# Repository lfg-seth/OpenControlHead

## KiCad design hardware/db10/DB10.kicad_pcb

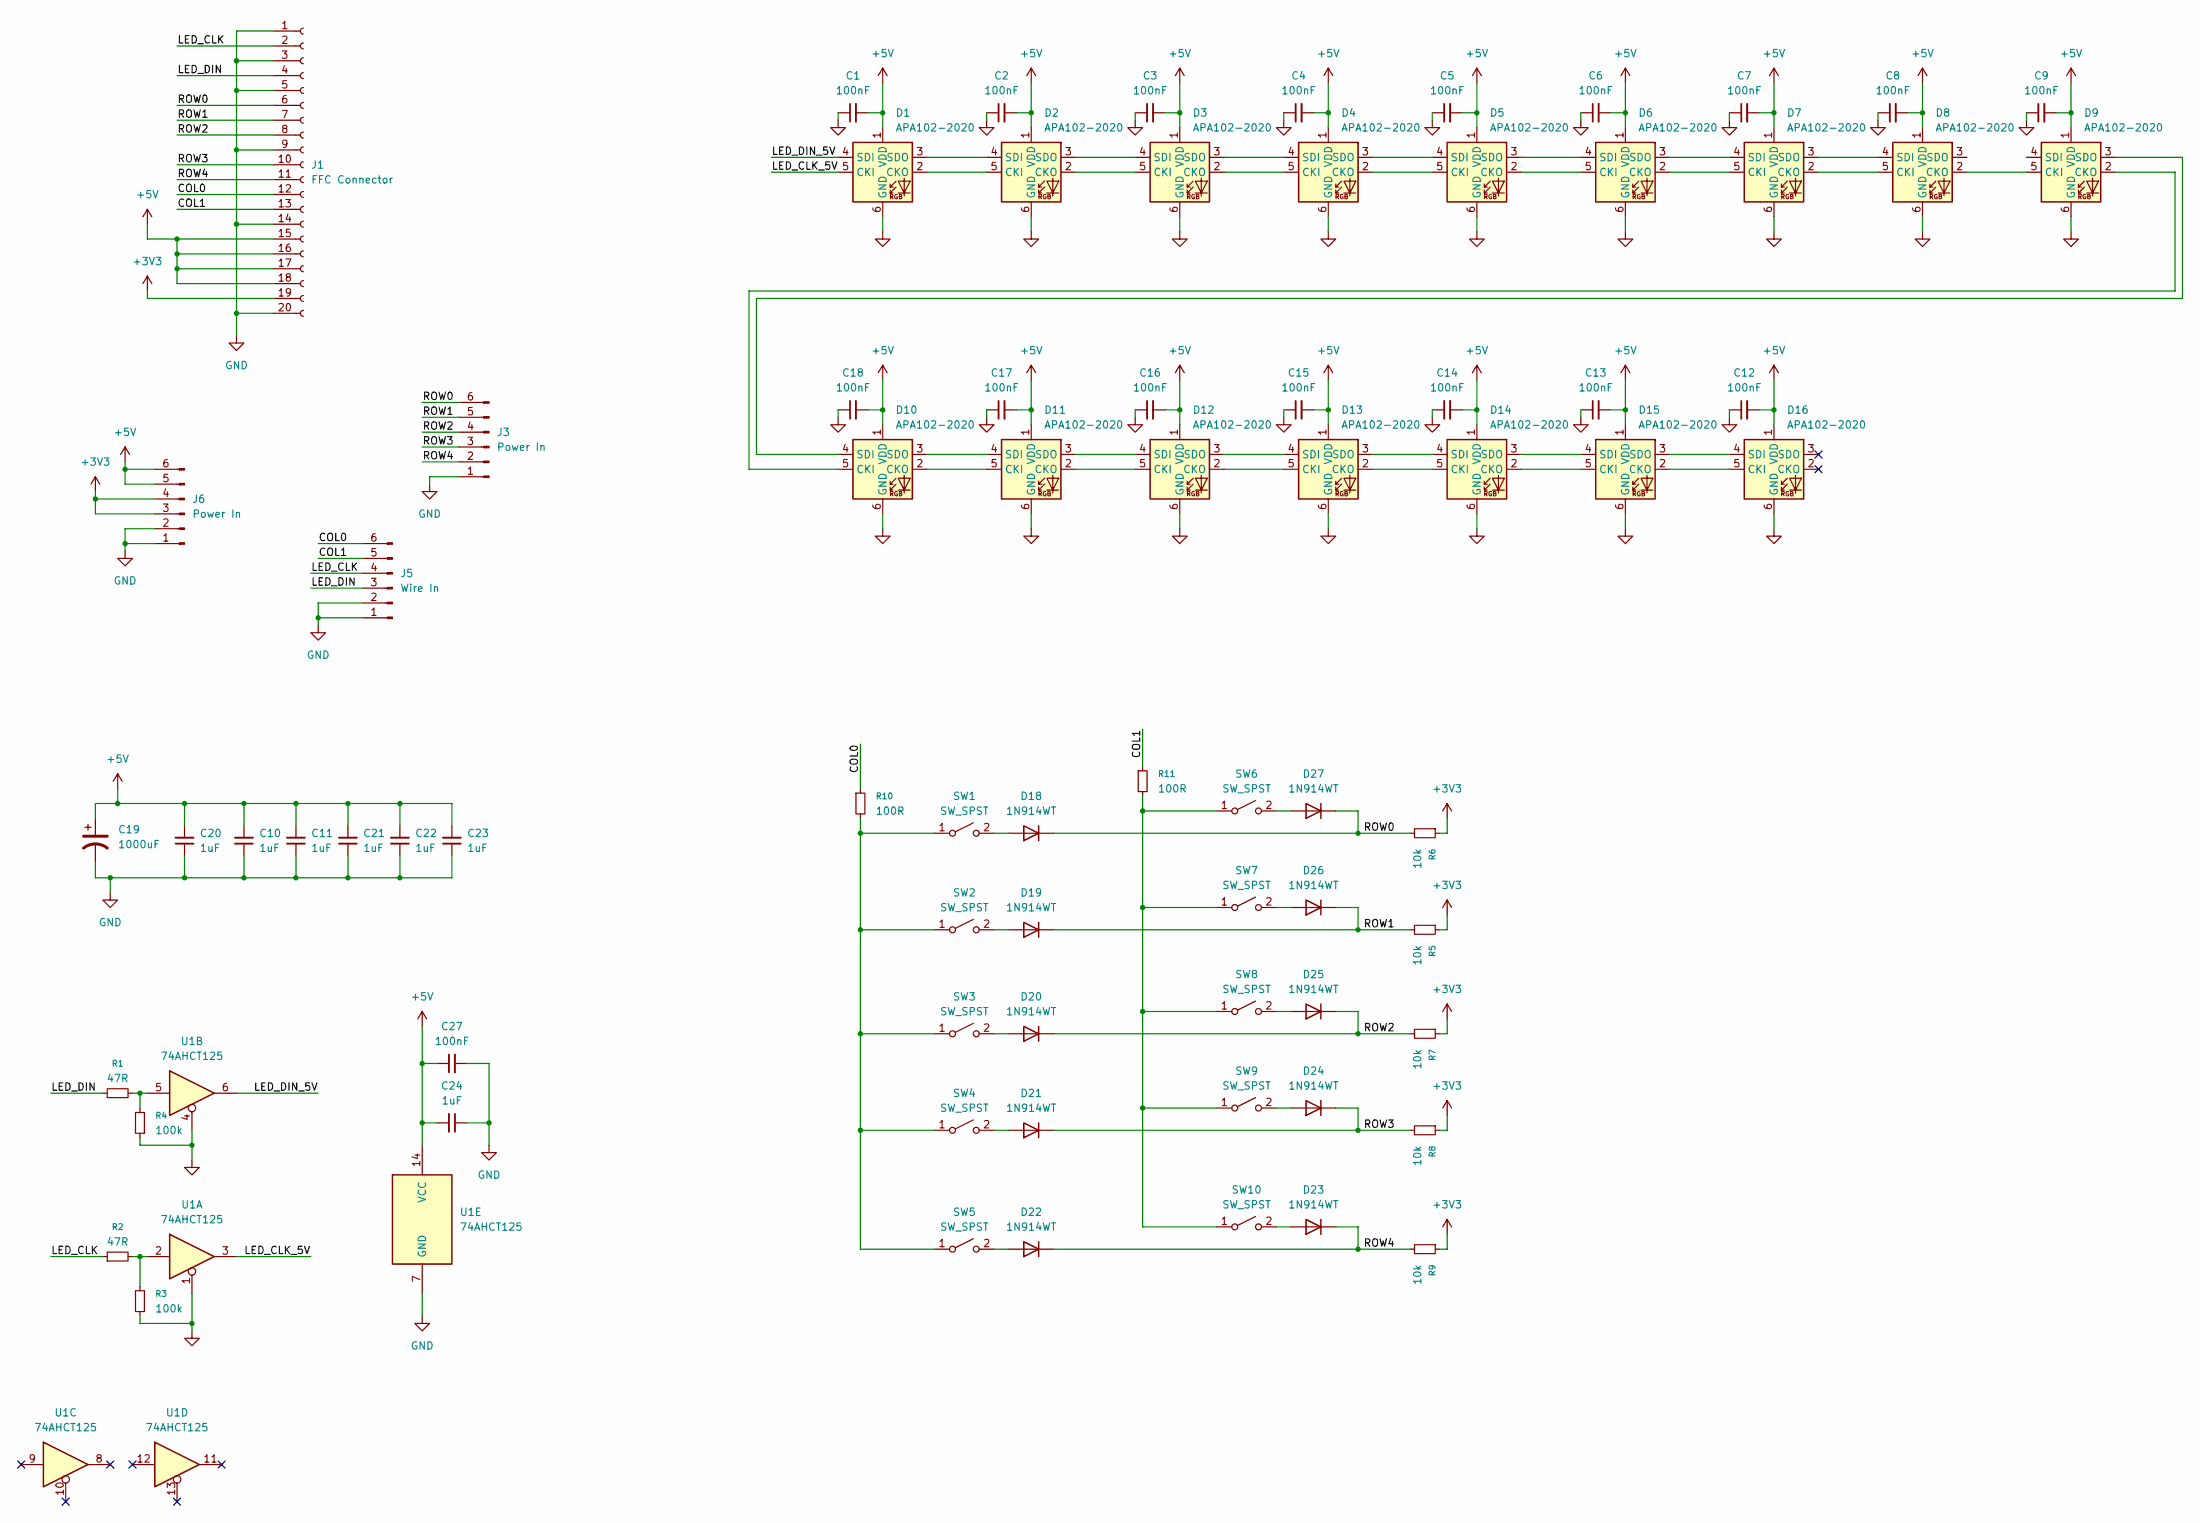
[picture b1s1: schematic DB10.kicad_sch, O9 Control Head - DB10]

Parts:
C1, C2, C3, C4, C5, C6, C7, C8, C9, C12, C13, C14, C15, C16, C17, C18, C27: 100nF; C_0603_1608Metric_Pad1.08x0.95mm_HandSolder
C10, C11, C20, C21, C22, C23, C24: 1uF; C_0603_1608Metric_Pad1.08x0.95mm_HandSolder
C19: 1000uF; CP_Elec_8x6.7
D1, D2, D3, D4, D5, D6, D7, D8, D9, D10, D11, D12, D13, D14, D15, D16: APA102-2020; LED-APA102-2020
D18, D19, D20, D21, D22, D23, D24, D25, D26, D27: 1N914WT; D_SOD-323_HandSoldering
J1: FFC Connector; Hirose_FH12-20S-0.5SH_1x20-1MP_P0.50mm_Horizontal
J3, J6: Power In; SolderWire-0.5sqmm_1x06_P4.8mm_D0.9mm_OD2.3mm
J5: Wire In; SolderWire-0.5sqmm_1x06_P4.8mm_D0.9mm_OD2.3mm
R1, R2: 47R; R_0603_1608Metric_Pad0.98x0.95mm_HandSolder
R3, R4: 100k; R_0603_1608Metric_Pad0.98x0.95mm_HandSolder
R5, R6, R7, R8, R9: 10k; R_0603_1608Metric_Pad0.98x0.95mm_HandSolder
R10, R11: 100R; R_0603_1608Metric_Pad0.98x0.95mm_HandSolder
SW1, SW2, SW3, SW4, SW5, SW6, SW7, SW8, SW9, SW10: SW_SPST; SW_SPST_TL3342
U1: 74AHCT125; SOIC-14_3.9x8.7mm_P1.27mm

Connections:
+3V3: J1.19, J6.3, J6.4, R5.1, R6.1, R7.1, R8.1, R9.1
+5V: C1.2, C2.2, C3.2, C4.2, C5.2, C6.2, C7.2, C8.2, C9.2, C10.2, C11.2, C12.2, C13.2, C14.2, C15.2, C16.2, C17.2, C18.2, C19.1, C20.2, C21.2, C22.2, C23.2, C24.2, C27.1, D1.1 (VDD), D2.1 (VDD), D3.1 (VDD), D4.1 (VDD), D5.1 (VDD), D6.1 (VDD), D7.1 (VDD), D8.1 (VDD), D9.1 (VDD), D10.1 (VDD), D11.1 (VDD), D12.1 (VDD), D13.1 (VDD), D14.1 (VDD), D15.1 (VDD), D16.1 (VDD), J1.15, J1.16, J1.17, J1.18, J6.5, J6.6, U1.14 (VCC)
/COL0: J1.12, J5.6, R10.1
/COL1: J1.13, J5.5, R11.1
/LED_CLK: J1.2, J5.4, R2.1
/LED_CLK_5V: D1.5 (CKI), U1.3
/LED_DIN: J1.4, J5.3, R1.1
/LED_DIN_5V: D1.4 (SDI), U1.6
/ROW0: D18.1 (K), D27.1 (K), J1.6, J3.6, R6.2
/ROW1: D19.1 (K), D26.1 (K), J1.7, J3.5, R5.2
/ROW2: D20.1 (K), D25.1 (K), J1.8, J3.4, R7.2
/ROW3: D21.1 (K), D24.1 (K), J1.10, J3.3, R8.2
/ROW4: D22.1 (K), D23.1 (K), J1.11, J3.2, R9.2
GND: C1.1, C2.1, C3.1, C4.1, C5.1, C6.1, C7.1, C8.1, C9.1, C10.1, C11.1, C12.1, C13.1, C14.1, C15.1, C16.1, C17.1, C18.1, C19.2, C20.1, C21.1, C22.1, C23.1, C24.1, C27.2, D1.6 (GND), D2.6 (GND), D3.6 (GND), D4.6 (GND), D5.6 (GND), D6.6 (GND), D7.6 (GND), D8.6 (GND), D9.6 (GND), D10.6 (GND), D11.6 (GND), D12.6 (GND), D13.6 (GND), D14.6 (GND), D15.6 (GND), D16.6 (GND), J1.1, J1.3, J1.5, J1.9, J1.14, J1.20, J3.1, J5.1, J5.2, J6.1, J6.2, R3.1, R4.1, U1.1, U1.4, U1.7 (GND)
unnamed: D1.2 (CKO), D2.5 (CKI)
unnamed: D1.3 (SDO), D2.4 (SDI)
unnamed: D2.2 (CKO), D3.5 (CKI)
unnamed: D2.3 (SDO), D3.4 (SDI)
unnamed: D3.2 (CKO), D4.5 (CKI)
unnamed: D3.3 (SDO), D4.4 (SDI)
unnamed: D4.2 (CKO), D5.5 (CKI)
unnamed: D4.3 (SDO), D5.4 (SDI)
unnamed: D5.2 (CKO), D6.5 (CKI)
unnamed: D5.3 (SDO), D6.4 (SDI)
unnamed: D6.2 (CKO), D7.5 (CKI)
unnamed: D6.3 (SDO), D7.4 (SDI)
unnamed: D7.2 (CKO), D8.5 (CKI)
unnamed: D7.3 (SDO), D8.4 (SDI)
unnamed: D8.2 (CKO), D9.5 (CKI)
unnamed: D9.2 (CKO), D10.5 (CKI)
unnamed: D10.2 (CKO), D11.5 (CKI)
unnamed: D9.3 (SDO), D10.4 (SDI)
unnamed: D10.3 (SDO), D11.4 (SDI)
unnamed: D11.2 (CKO), D12.5 (CKI)
unnamed: D11.3 (SDO), D12.4 (SDI)
unnamed: D12.2 (CKO), D13.5 (CKI)
unnamed: D12.3 (SDO), D13.4 (SDI)
unnamed: D13.2 (CKO), D14.5 (CKI)
unnamed: D13.3 (SDO), D14.4 (SDI)
unnamed: D14.2 (CKO), D15.5 (CKI)
unnamed: D14.3 (SDO), D15.4 (SDI)
unnamed: D15.2 (CKO), D16.5 (CKI)
unnamed: D15.3 (SDO), D16.4 (SDI)
unnamed: D18.2 (A), SW1.2 (B)
unnamed: D19.2 (A), SW2.2 (B)
unnamed: D20.2 (A), SW3.2 (B)
unnamed: D21.2 (A), SW4.2 (B)
unnamed: D22.2 (A), SW5.2 (B)
unnamed: D23.2 (A), SW10.2 (B)
unnamed: D24.2 (A), SW9.2 (B)
unnamed: D25.2 (A), SW8.2 (B)
unnamed: D26.2 (A), SW7.2 (B)
unnamed: D27.2 (A), SW6.2 (B)
unnamed: R1.2, R4.2, U1.5
unnamed: R2.2, R3.2, U1.2
unnamed: R10.2, SW1.1 (A), SW2.1 (A), SW3.1 (A), SW4.1 (A), SW5.1 (A)
unnamed: R11.2, SW6.1 (A), SW7.1 (A), SW8.1 (A), SW9.1 (A), SW10.1 (A)

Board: 2 copper layers, 76 parts (0 on the bottom side), 57 nets, no tracks yet.

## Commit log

2025-11-08 Add UI App
2025-11-08 Add hardware
2025-11-08 Add pico firmware
2025-11-08 add files
2025-11-10 update design
2025-11-10 Add scaffolding for pcm.py
2025-11-10 update can docs
2025-11-11 Update logging
2025-11-11 add switch controller scaffold
2025-11-11 Refactor PCM and Switch imports; enhance LogicalSwitch logging and functionality
2025-11-11 Add cycle method to LogicalSwitch for multi-state behavior
2025-11-11 Enhance Bridge class with switch state management and toggle functionality
2025-11-11 Enhance LightsPage with Front Lights toggle functionality and update LogicalSwitch toggle method with logging
2025-11-11 chmod run.sh
2025-11-11 Refactor run.sh to improve Python version handling and virtual environment setup
2025-11-11 Update Python version requirements and allowed candidates in configuration
2025-11-11 Fix syntax error in Python candidates array in run.sh
2025-11-11 Comment out virtual environment creation logic in run.sh
2025-11-11 revert run.sh
2025-11-11 Remove logs page
2025-11-11 Remove unnecessary anchors from controlsPanel in LightsPage.qml
2025-11-11 Comment out anchor properties in LightsPage.qml for Image and Column elements
2025-11-11 Restore anchor properties for Image and Column elements in LightsPage.qml
2025-11-11 Comment out anchors for Image in LightsPage.qml and restore anchors for controlsPanel
2025-11-11 Restore anchors for Image in LightsPage.qml
2025-11-11 Refactor hardware layer initialization in app.py to streamline switch registration and remove redundant code
2025-11-11 Refactor logging in QmlLogBridge and enhance button handling in Bridge class
2025-11-11 Update button mapping in Bridge class to use descriptive names
2025-11-11 Add 4ch_pcm scaffold
2025-11-12 Add autosave file for 4-channel PCM schematic
2025-11-14 save kicad
2025-11-14 working. But prep for refactor
2025-11-14 refactor
2025-11-14 Remove channelbinding
2025-11-14 update docs
2025-11-14 Update Serial worker to handle spaces
2025-11-14 Refactor Bridge class documentation to clarify SerialWorker integration; add cron.py file.
2025-11-14 Adjust image anchoring and size in LightsPage; add properties for front lights switch in app.py
2025-11-14 Add todo
2025-11-15 add notes
2025-11-15 update lights
2025-11-15 Update lights page
2025-11-21 Add python-can dependency and enhance PCM functionality
2025-11-21 Refactor PCMManager to use explicit callback parameter for CAN message handling
2025-11-22 Enhance PCM functionality with 29-bit ID support and refactor CAN message handling
2025-11-22 Add Macro Control to can doc
2025-11-22 Add macro control for Front Flashers and implement PCMMacro class
2025-11-22 Add Flashers logical switch and update button mapping
2025-12-03 add pico firmware for pcm and switchpanel
2025-12-03 Update dir
2025-12-03 add can monitor
2025-12-03 update script
2025-12-03 remove sudo code
2025-12-18 update channels
